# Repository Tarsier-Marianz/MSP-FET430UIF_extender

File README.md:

# MSP-FET430UIF_extender

A prototype board serve as an extender for *MSP430 USB-Debug Interface* ([**MSP-FET430UIF**](http://www.ti.com/tool/MSP-FET430UIF)) Programmer of [**Texas Instrument**](http://www.ti.com/).

## Board Preview

# Credits
[KiCAD IDE](http://kicad-pcb.org/) letting me use a free software in designing PCB.

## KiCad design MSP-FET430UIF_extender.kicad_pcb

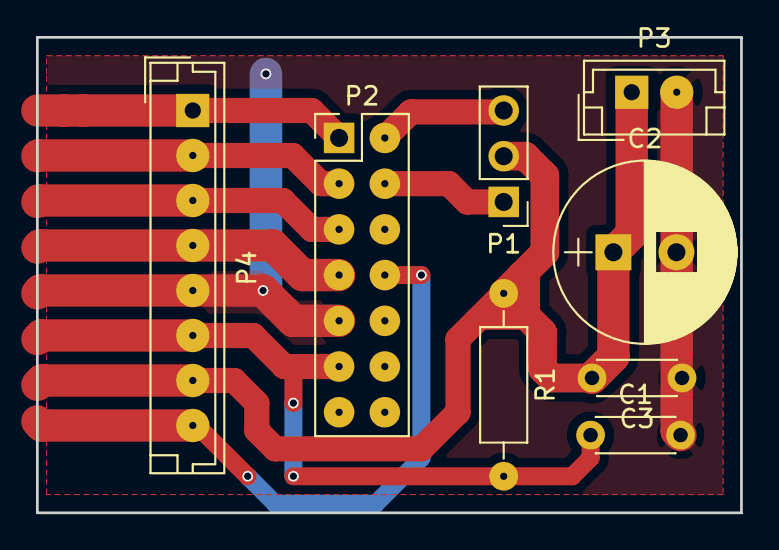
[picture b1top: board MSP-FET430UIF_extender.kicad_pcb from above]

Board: 2 copper layers, 39.1 x 26.4 mm, 8 parts (0 on the bottom side), 10 nets.

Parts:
C1: 1nF; C_Disc_D4.3mm_W1.9mm_P5.00mm
C2: 10uF 16V; CP_Radial_D10.0mm_P3.50mm
C3: 0.1uF; C_Disc_D4.3mm_W1.9mm_P5.00mm
P1: CONN_01X03; Pin_Header_Straight_1x03_Pitch2.54mm
P2: CONN_02X07; Pin_Header_Straight_2x07_Pitch2.54mm
P3: CONN_01X02; JST_EH_B02B-EH-A_02x2.50mm_Straight
P4: CONN_01X08; JST_EH_B08B-EH-A_08x2.50mm_Straight
R1: 47K; R_Axial_DIN0207_L6.3mm_D2.5mm_P10.16mm_Horizontal

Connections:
/GND: C1.2, C2.2, C3.1, P2.9, P3.2, P4.5
/RST: C1.1, P2.11, P4.6, R1.2
/TCK: P2.7, P4.4
/TDI: P2.3, P4.2
/TDO: P2.1, P4.1
/TEST: P2.8, P4.8
/TMS: P2.5, P4.3
/VCC: C2.1, C3.2, P1.2, P3.1, P4.7, R1.1
/VCC_TARGET: P1.1, P2.4
/VCC_TOOL: P1.3, P2.2

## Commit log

2018-03-21 +add circuit schematic diagram
2018-03-21 +netlist labels
2018-03-21 +annotate schematic components
2018-03-21 +adding components footprints adn generate netlist
2018-03-21 +add pcb layout
2018-03-22 *finalized pcb layout
2018-03-22 +readme repo overview
2018-08-04 *readme naming correction
2018-11-07 *remapping sysmbol into latest version of kicad
2018-11-07 +adding rescue folder from previous version of project
2018-11-07 *screenshot
